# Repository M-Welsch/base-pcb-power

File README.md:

# Backup Server Power PCB

This circuit board has the following responsibilities

- take 12V Power connection from outside
- generate 5V and 3.3V
- supply BananaPi and HDD
- switch power to BananaPi and HDD (separately)
- take BananaPi M1
- connect to HMI Board

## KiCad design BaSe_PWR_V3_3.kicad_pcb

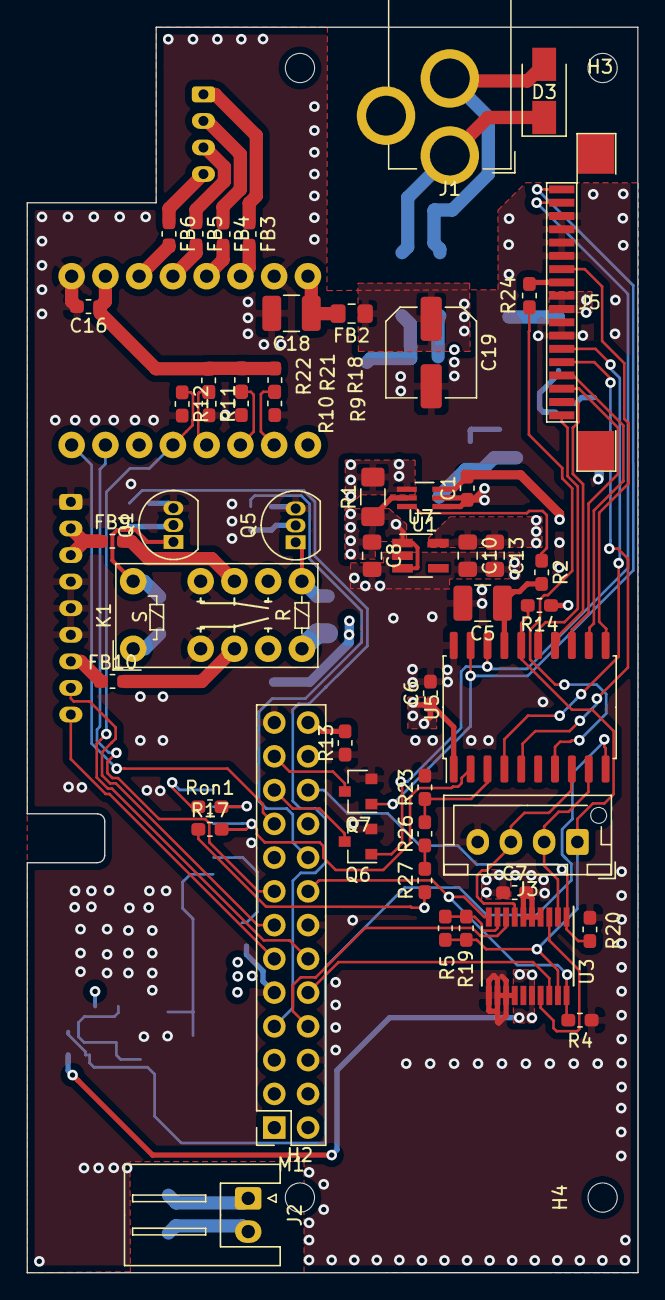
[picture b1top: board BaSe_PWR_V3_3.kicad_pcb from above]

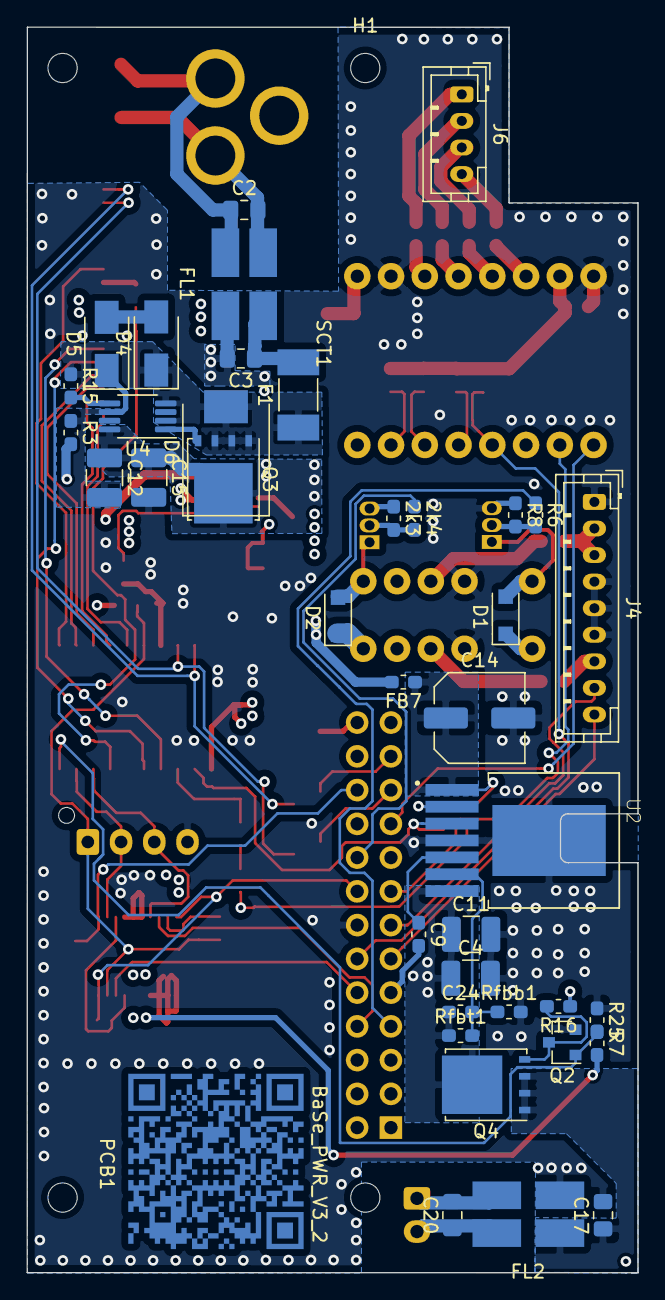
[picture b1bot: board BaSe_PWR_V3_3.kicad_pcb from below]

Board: 4 copper layers, 46.0 x 93.7 mm, 110 parts (41 on the bottom side), 78 nets.

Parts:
2k3: 47k; R_0603_1608Metric_Pad1.05x0.95mm_HandSolder
2k4: 1k2; R_0603_1608Metric_Pad1.05x0.95mm_HandSolder
C1, C6, C7, C16: 100nF; C_0603_1608Metric_Pad1.05x0.95mm_HandSolder
C2, C3, C8, C10, C13, C17, C20: 1µF; C_0805_2012Metric_Pad1.15x1.40mm_HandSolder
C4, C11: 100µF; C_1210_3225Metric_Pad1.42x2.65mm_HandSolder
C5, C15, C18: 10µF; C_1210_3225Metric_Pad1.42x2.65mm_HandSolder
C9: 10nF; C_0603_1608Metric_Pad1.05x0.95mm_HandSolder
C12: 47nF; C_1210_3225Metric_Pad1.42x2.65mm_HandSolder
C14, C19: 220µF; C_Elec_6.3x7.7
C24: 1nF; C_0603_1608Metric_Pad1.05x0.95mm_HandSolder
Cable_BPi_SPLY_preconfected1, Cable_BPi_SPLY_preconfected2: ASXHSXH22K51; BOM_ITEM
Cable_HDD_ENDSW_preconfected2: ASPHSPH24K152; BOM_ITEM
Cable_Stepper_preconfected1, Cable_Stepper_preconfected2, Cable_Stepper_preconfected3, Cable_Stepper_preconfected4: ASPHSPH24K51‎; BOM_ITEM
Conn_Socket_BPi_SPLY1: XHP-2; BOM_ITEM
Conn_Socket_BPi_SPLY_atJ5: XHP-2; BOM_ITEM
Conn_Socket_PWR_HDD1: PHR-9; BOM_ITEM
Conn_Socket_Stepper1: PHR-4; BOM_ITEM
Conn_Socket_at_Stepper1: PHR-6; BOM_ITEM
D1, D2: 1N4148; D_SOD-123F
D3: 824501121; D_SMA
D4, D5: NO; D_SMA
D6: NO; D_SMC
F1: Fuse; Fuse_Littelfuse-NANO2-451_453
FB2: 742792093; L_0805_2012Metric_Pad1.15x1.40mm_HandSolder
FB3, FB4, FB5, FB6, FB7, FB9, FB10: 742792602; L_0603_1608Metric_Pad1.05x0.95mm_HandSolder
FFC_Cable1: 0151670333; BOM_ITEM
FL1, FL2: CM2021Y330R-10; CMC_Laird_CM2021Y330R-10
H1, H2, H3, H4: MountingHole; MountingHole_2.2mm_M2
J1: 12V Power In; BarrelJack_Wuerth_6941xx301002
J2: BPi Supply; JST_XH_S2B-XH-A_1x02_P2.50mm_Horizontal
J3: DebugAtTiny; JST_XH_B4B-XH-AM_1x04_P2.50mm_Vertical
J4: B9B-PH-K-S(LF)(SN); JST_PH_B9B-PH-K_1x09_P2.00mm_Vertical
J5: Molex 0522071860; Conn_FFC_Molex_52207-1860
J6: B4B-PH-K-S(LF)(SN); JST_PH_B4B-PH-K_1x04_P2.00mm_Vertical
K1: EC2-12TNU; Relay_Kemet_EC2-12TNU
M1: BananaPi_M1; BananaPi-M1
PCB1: BaSe_PWR_V3_2
Q1, Q5: BS170; TO-92_Inline
Q2, Q6, Q7: BSS123; SOT-23
Q3: BSC028N06LS3; TDSON-8-1
Q4: BSC093N04LS; TDSON-8-1
R1: 1m; R_1206_3216Metric_Pad1.42x1.75mm_HandSolder
R2, R4, R8, R14, R15, R16, R17, R20, R25: 47k; R_0603_1608Metric_Pad1.05x0.95mm_HandSolder
R3: 1k; R_0603_1608Metric_Pad1.05x0.95mm_HandSolder
R5, R19: 10k; R_0603_1608Metric_Pad1.05x0.95mm_HandSolder
R6, R24: 1k2; R_0603_1608Metric_Pad1.05x0.95mm_HandSolder
R7, R18, R26, R27: NO; R_0603_1608Metric_Pad1.05x0.95mm_HandSolder
R9, R10, R11: 0R; R_0603_1608Metric_Pad1.05x0.95mm_HandSolder
R12, R21, R22: 100k; R_0603_1608Metric_Pad1.05x0.95mm_HandSolder
R13, R23: 0; R_0603_1608Metric_Pad1.05x0.95mm_HandSolder
Rfbb1: 1,87K; R_0603_1608Metric_Pad1.05x0.95mm_HandSolder
Rfbt1: 10k; R_0603_1608Metric_Pad1.05x0.95mm_HandSolder
Ron1: 47k; R_0603_1608Metric_Pad1.05x0.95mm_HandSolder
SCT1: A4988_Module
U1: INA212; SOT-363_SC-70-6_Handsoldering
U2: LMZ12003; LMZ12003_Handsolder
U3: ADG734; TSSOP-20_4.4x6.5mm_P0.65mm
U4: LTC4359-MS8; MSOP-8_3x3mm_P0.65mm_Py0.45mm
U5: ATtiny816-S; SOIC-20W_7.5x12.8mm_P1.27mm
U7: AP2204K-3.3; SOT-23-5_HandSoldering

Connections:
+3V3: C16.1, M1.1, R18.1, R21.1, R22.1, SCT1.10
+3V3_STBY: C1.2, C6.1, C7.1, C10.1, C13.1, R7.2, R14.1, R17.1, R27.1, U1.3, U3.16, U5.1, U7.5
+5V: C4.1, C11.1, C24.1, J5.9, J5.10, K1.5, Q4.5, Rfbt1.1, U2.7
+12V: C8.1, C19.1, D1.1, D2.1, FB2.1, FB7.2, K1.1, K1.6, K1.8, R1.1, R16.1, U1.5, U7.1, U7.3
/5V_EN: R17.2, U2.3, U5.2
/5V_Ron: Ron1.2, U2.2
/12V_Prot: C12.1, C15.1, D6.1, Q3.5, R1.2, U1.4, U4.8
/12V_nProt: D4.1, D6.2, F1.1, Q3.1, Q3.2, Q3.3, R15.1, U4.2, U4.4
/+5V_HDD: FB10.2, K1.4
/+5V_HDD_flt: FB10.1, J4.7
/+12V_HDD: FB9.2, K1.9
/+12V_HDD_flt: FB9.1, J4.2, J4.3
/DC_IN+: C2.2, D3.1, FL1.1, J1.1
/DC_IN-: C2.1, D3.2, FL1.2, J1.2
/DIS_BPi_SPLY: Q2.1, R7.1, R25.2, U5.10
/Dis_DB4: J5.4, U5.12
/Dis_DB5: J5.3, U5.13
/Dis_DB6: J5.2, U5.14
/Dis_DB7: J5.1, U5.15
/Dis_E: J5.5, U5.5
/Dis_PWM: J5.12, U5.11
/Dis_RS: J5.6, U5.4
/EN_attiny_link: M1.22, R20.1, U3.1
/LED_HMI: J5.11, R24.2
/LED_HMI_attiny: R24.1, U5.7
/MS1: R9.1, R18.2, SCT1.2
/MS2: R10.1, R21.2, SCT1.3
/MS3: R11.1, R22.2, SCT1.4
/RxD_BPi: M1.10, U3.18
/RxD_attiny: J3.3, U3.7, U5.8
/SW_HDD_Off: 2k4.1, M1.18
/SW_HDD_On: M1.7, R6.1
/Step_1A: FB5.2, SCT1.12
/Step_1B: FB6.2, SCT1.11
/Step_2A: FB4.2, SCT1.13
/Step_2B: FB3.2, SCT1.14
/Stepper_Dir: M1.19, SCT1.8
/Stepper_Step: M1.15, SCT1.7
/Stepper_~Reset: M1.12, R12.1, SCT1.5
/Taster_0: J5.17, Q6.1, U5.18
/Taster_1: J5.18, Q7.1, U5.19
/TxD_BPi: M1.8, U3.8
/TxD_attiny: J3.2, U3.2, U5.9
/TxD_attiny_prot: U3.3, U3.17
/V_meas: R2.1, U1.6
/V_meas_flt: C5.1, R2.2, U5.17
/Version: R23.1, R26.2, U5.3
/Vin_Buck: C14.1, FB7.1, Ron1.1, U2.1
/Vin_Stepper: C18.1, FB2.2, SCT1.16
/attiny_program_~communicate: M1.16, R4.1, U3.10, U3.20
/attiny_~reset: J3.1, R5.1, R14.2, R19.1, U3.19, U5.16
/rev2_~rev3: M1.26, R13.2
/~Endswitch_Docked: J4.8, M1.13
/~Endswitch_Undocked: J4.9, M1.11
/~Taster_0: M1.21, Q6.3
/~Taster_1: M1.23, Q7.3
GND: 2k3.1, C1.1, C3.2, C4.2, C5.2, C6.2, C7.2, C8.2, C9.2, C10.2, C11.2, C13.2, C14.2, C15.2, C16.2, C17.2, C18.2, C19.2, FL1.3, FL2.4, J3.4, J4.1, J4.4, J4.5, J4.6, J5.7, J5.8, J5.13, J5.14, J5.15, J5.16, K1.3, K1.10, M1.6, M1.9, M1.14, M1.20, M1.25, Q1.3, Q2.2, Q5.3, Q6.2, Q7.2, R3.2, R4.2, R8.1, R9.2, R10.2, R11.2, R12.2, R13.1, R20.2, R23.2, R25.1, Rfbb1.2, SCT1.9, SCT1.15, U1.1, U1.2, U2.4, U2.8, U3.4, U3.5, U3.6, U3.11, U3.12, U3.13, U3.14, U5.20, U7.2
unnamed: 2k3.2, 2k4.2, Q5.2
unnamed: C3.1, F1.2, FL1.4
unnamed: C9.1, U2.5
unnamed: C12.2, D5.1, R3.1, U4.6
unnamed: C17.1, FL2.3, Q4.1, Q4.2, Q4.3
unnamed: C20.1, FL2.2, J2.2
unnamed: C20.2, FL2.1, J2.1
unnamed: C24.2, Rfbb1.1, Rfbt1.2, U2.6
unnamed: D1.2, K1.12, Q1.1
unnamed: D2.2, K1.7, Q5.1
unnamed: D4.2, D5.2
unnamed: FB3.1, J6.1
unnamed: FB4.1, J6.2
unnamed: FB5.1, J6.3
unnamed: FB6.1, J6.4
unnamed: Q1.2, R6.2, R8.2
unnamed: Q2.3, Q4.4, R16.2
unnamed: Q3.4, U4.1
unnamed: R15.2, U4.5
unnamed: R5.2, R19.2, U3.9
unnamed: R26.1, R27.2

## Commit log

2022-03-30 first version. Built up similarily
2022-03-30 still LEGO
2022-03-30 v3 with raspberry pi 4
2022-03-30 version with bananapi. Manufactured by jlcpcb and used in hw_rev3b
2022-03-30 replace analog switches by cheaper ones
